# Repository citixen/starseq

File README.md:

# starseq — project overview

This project and all files in it represent the state of the project as it was during EMF Camp 2026, where it ran as an installation (in the baking sun) for 4 days. It largely worked without incident for that time and the concept and implementation are at least a bit proven. However, the project is offered as-is and without any ability to support it further if you decide to try building one for yourself. It all works in my build, but that doesn't mean it will for you. I may have forgotten critical setup components, and I may have done something weird and forgotten to document it. Sorry if I did. I've also not really documented any of the specifics of how I wired it together in my build. It was horrible spaghetti (see pics) and you can definitely do better just using the pin allocations in the code to guide you. Best of luck! Use this as a jumping off point to something bigger and better! I know I will!

---

## what starseq is

**starseq** is an 8-track MIDI step sequencer whose musical content is generated from the real-time positions of naked-eye-visible stars in the sky above the instrument's physical location. Each of the 8 tracks claims a wedge ("slice") of the compass — a band of azimuth and a brightness threshold — and turns whichever stars currently sit inside that wedge into a step sequence: azimuth decides *when* (which step) a note falls, altitude decides *what pitch*, and brightness/colour decide *how loud* and *how long*. Because the sky moves, the sequences drift and evolve on their own, in real astronomical time or sped up/slowed/reversed via a simulated clock. Planets and constellation lines are drawn for visual context only currently — but the data is there for future uses.

The instrument is physically and electronically a three-tier system:

```
┌──────────────────────┐      ┌──────────────────────┐     ┌─────────────────────┐
│ 8 × Instrument       │      │ Controller Interface │     │ Sequencer           │
│ Controllers          │────▶│  (aggregator)        │────▶│ (Raspberry Pi 5)    │
│ (one per track)      │ UART │ RP2040 Pico          │ UART│ Sky engine, MIDI,   │
│ 9 pots + 2 switches  │      │                      │     │ display, output     │
│ + button + OLED      │      │                      │     │                     │
└──────────────────────┘      └──────────────────────┘     └─────────────────────┘
     ESP32-S3 DevKit             8-port aggregator            pygame + skyfield
     per track                  → single uplink               + MIDI + GPIO
```

A performer turns physical pots on 8 identical hand controllers; those settings flow up through an aggregating interface board to a Raspberry Pi, which combines them with live sky data to produce and play an 8-track MIDI sequence, rendered simultaneously as a star-dome visualisation.

The instrument is housed in a standard cheap 104hp eurorack case, with some cheap bulkhead pass-thrus to get USB and HDMI from the Pi outside the case, and to get power in.

---

## tier 1 — instrument controller (one per track, ×8)

**Hardware:** ESP32-S3 DevKit C-1 (cheap - and has 2 x 12-bit SAR ADCs). Per unit: 9 potentiometers, 2 SPDT switches (Mute/Stop; Mono/Poly), 1 momentary push-button (play direction), a 128×64 SSD1306 2 colour (yellow/blue) OLED over I2C (mounted inverted, yellow  strip at the bottom), and a UART link out to the Controller Interface. The PCB files are included for the version used at EMF 26. These were made quickly and down to a price. Better board layouts and control configurations can be achieved!

**Role:** turn physical control positions into a per-track parameter packet and keep the OLED showing current state.

In the published firmware, all 9 pots are live simultaneously on a single page (an earlier multi-page design was collapsed to one page for simplicity). Each pot drives one parameter directly: length, base note, note range, slice centre, step divider, slice width, play mode, slice brightness, and duration max (which rescales live across `1…current length`). The two switches and the button cover mute/stop, mono/poly, and play-direction toggle. Parameters that are sent from the controller but which no longer have a dedicated pot in this  revision — velocity lo/hi, duration lo, parameter mode, MIDI channel — are  held at fixed firmware defaults but are still transmitted in full on every  packet, because **the wire format was deliberately left unchanged** from an  earlier, fuller-featured revision. This means the interface and sequencer  require no changes to accept this simplified controller, and a future firmware  revision could re-expose those parameters on interface pages without touching  downstream code.

The controller debounces inputs, applies deadbanding to pot readings to try  to avoid flooding the serial link with jitter, and transmits change-driven updates plus a periodic heartbeat. It persists its working state to the ESP32's flash-backed NVS (a packed, versioned, CRC-checked 22-byte struct), so a power cycle resumes the previous session instead of resetting to defaults — with **pick-up logic** at boot only: a restored pot value is shown with a directional arrow on the OLED until the performer physically turns that pot through the stored value, at which point it goes live.

---

## tier 2 — controller interface (aggregator)

**Hardware:** a single Raspberry Pi Pico (RP2040), with 8 independent PIO-UART port pairs (one RX/TX pair per controller) plus one hardware UART uplink to the Raspberry Pi. All built onto a small vero board, along with power distribution for the controllers. Takes in a single USB-C connection for 5V.

**Role:** a hardware-agnostic multiplexer. It runs 8 concurrent per-port receivers, validates and decodes each controller's packet (frame boundaries, protocol version, CRC, field ranges), maintains a live state table (one record per controller, with sequence number, last-RX timestamp, and a waiting/online/stale/offline status derived from timeout), and republishes that aggregated state upstream to the Pi as a single serial stream. A single-port fault never blocks the other 7 ports.

Two upstream message shapes exist: periodic **full snapshots** (all 8 controller records in one packet, sent roughly every 400 ms) and **delta packets** (a single controller's record, sent immediately whenever a field changes beyond a small deadband). This keeps the uplink responsive to live pot movement without needing to stream continuously.

---

## tier 3 — sequencer (Raspberry Pi 5)

**Hardware:** a Raspberry Pi 5, with a serial connection to the interface board, a 20 pulse rotary encoder and an SPDT connected to GPIO pins. Outputs HDMI, and has USB connections - all passed through the case.

**Role:** the brain of the instrument. Runs headlessly, receives the  aggregated controller state over serial, computes the live sky, turns  sky + per-track parameters into MIDI, and renders everything to an HDMI/DSI display via pygame.

### architecture

The application is a set of daemon background threads (Serial RX, Input Handler, Sky Engine, Sequence Builder, Sequencer Engine, MIDI Clock Input, GPS Receiver) plus one blocking main-thread loop for the pygame display — pygame's video backend must own the main thread on Linux/the Pi. Shared state moves through thread-safe primitives only: per-track locks, bounded queues, and a lock-free double-buffered (plus one "pending") sequence store per track. The sequencer engine requests real-time (`SCHED_FIFO`) scheduling and is never allowed to block on sky computation, serial I/O, GPS parsing, or rendering.

### midi generation

1. **Sky Engine** recomputes, on a fixed ~250 ms interval, the alt/az of    every star in the Yale Bright Star Catalogue (via Skyfield/DE421) and of     7 planets, using a **simulated clock** that can run at real speed, be     frozen, fast-forwarded, or reversed (a discrete multiplier ladder from     ‑64× to 64×), or jumped to an explicit date via a preset events picker     or manual date fields. Only stars above the horizon and brighter than     magnitude 6.5 (naked-eye) survive into the published snapshot; planets     are published on a separate, sequencing-blind channel.
2. **Sequence Builder** takes each track's slice (`slice_centre` ±    `slice_width/2`, wrap-around handled mod 360) and `slice_brightness`    (mapped to a magnitude cutoff), filters the star snapshot down to that    track's candidate stars, buckets them into steps by azimuth, assigns each    a MIDI note from altitude (mapped onto the valid in-scale notes within    `base_note … base_note + note_range`), and picks which candidate(s) in a    step actually sound according to the track's **play mode** (random,    highest, lowest, middle, first, last, brightest, dimmest) and mono/poly    mode. Velocity comes from magnitude and duration from B‑V colour index    (or from static/per-loop-randomised values, depending on `param_mode`).    Loop-randomised tracks stage their next sequence in a third "pending"    buffer so a re-roll never disturbs a note already playing mid-loop; the    swap happens only at that track's own loop boundary.
3. **Sequencer Engine** is the real-time clock: internal PPQN-24 tick    generation or external MIDI clock, per-track step/tick accumulators so    tracks can run at independent step-dividers while staying phase-locked,    forward/reverse play direction, note-on/note-off scheduling, and MIDI    output. It also drives the flash events consumed by the display so that    firing notes visibly pulse on the star dome and sequencer grid in the    same colour as the track that's playing them.
4. **MIDI channel routing** is decoupled from whatever channel a controller    itself reports: a transport-bar **CH MODE** setting chooses between the    controller-launch default, sequential per-track channels, all-tracks-on-    one-channel, or trusting the controller's own reported channel.

### display

A pygame UI running at 30 fps shows a polar-projected star dome (stars, planet hexagon markers, constellation lines), an 8-row sequencer grid, and an always-visible transport bar (no modal menu — a single focus pointer moves around a flat ring of stops for location, view/brightness toggles, tempo, clock source, key/scale, polyphony limit, MIDI device, channel mode, and simulated time). Layout adapts automatically to portrait, landscape, or extreme-aspect screens, and three independent brightness toggles plus a 10-mode **VIEW** setting control how much of the sky, wedges, and note flashes are visible without ever touching what's actually being sequenced.

### inputs

A rotary encoder + SPDT play/stop switch (GPIO on the Pi) provide local transport control, with a keyboard fallback for headless/dev use. Location can come from config defaults, manual entry, a USB NMEA GPS receiver, or a built-in list of preset cities — switchable live, without a restart.

---

## end-to-end data flow

```
Pot/switch/button position (Instrument Controller)
   → smoothed, deadbanded, mapped to parameter range
   → packed into a 21-byte controller record, COBS-framed, CRC-8
   → UART to Controller Interface

Controller Interface
   → validated per-port, staged into a per-controller state table
   → status (waiting/online/stale/offline) derived from packet recency
   → re-aggregated into full (8-record) or delta (1-record) packets
   → COBS-framed, CRC-8, UART uplink to Raspberry Pi

Raspberry Pi — Serial RX thread
   → CRC-checked, decoded, written directly into that track's TrackState
     under its lock; sequence_dirty = True

Sky Engine (independent of the above)
   → simulated time → star & planet alt/az → filtered snapshot published

Sequence Builder
   → combines the track's parameters with the star snapshot
   → produces a step sequence (notes, velocities, durations)

Sequencer Engine
   → ticks, advances steps, fires MIDI Note On/Off, schedules flash events

MIDI Output + Display
   → notes/clock out over MIDI; star dome & grid rendered in sync
```

A single 21-byte controller record schema is shared verbatim across all three tiers — the Instrument Controller populates it, the Controller Interface forwards it unmodified, and the Sequencer is the only tier that interprets it semantically (resolving the step-divider index to an actual ratio, applying channel-mode overrides, etc.).

---

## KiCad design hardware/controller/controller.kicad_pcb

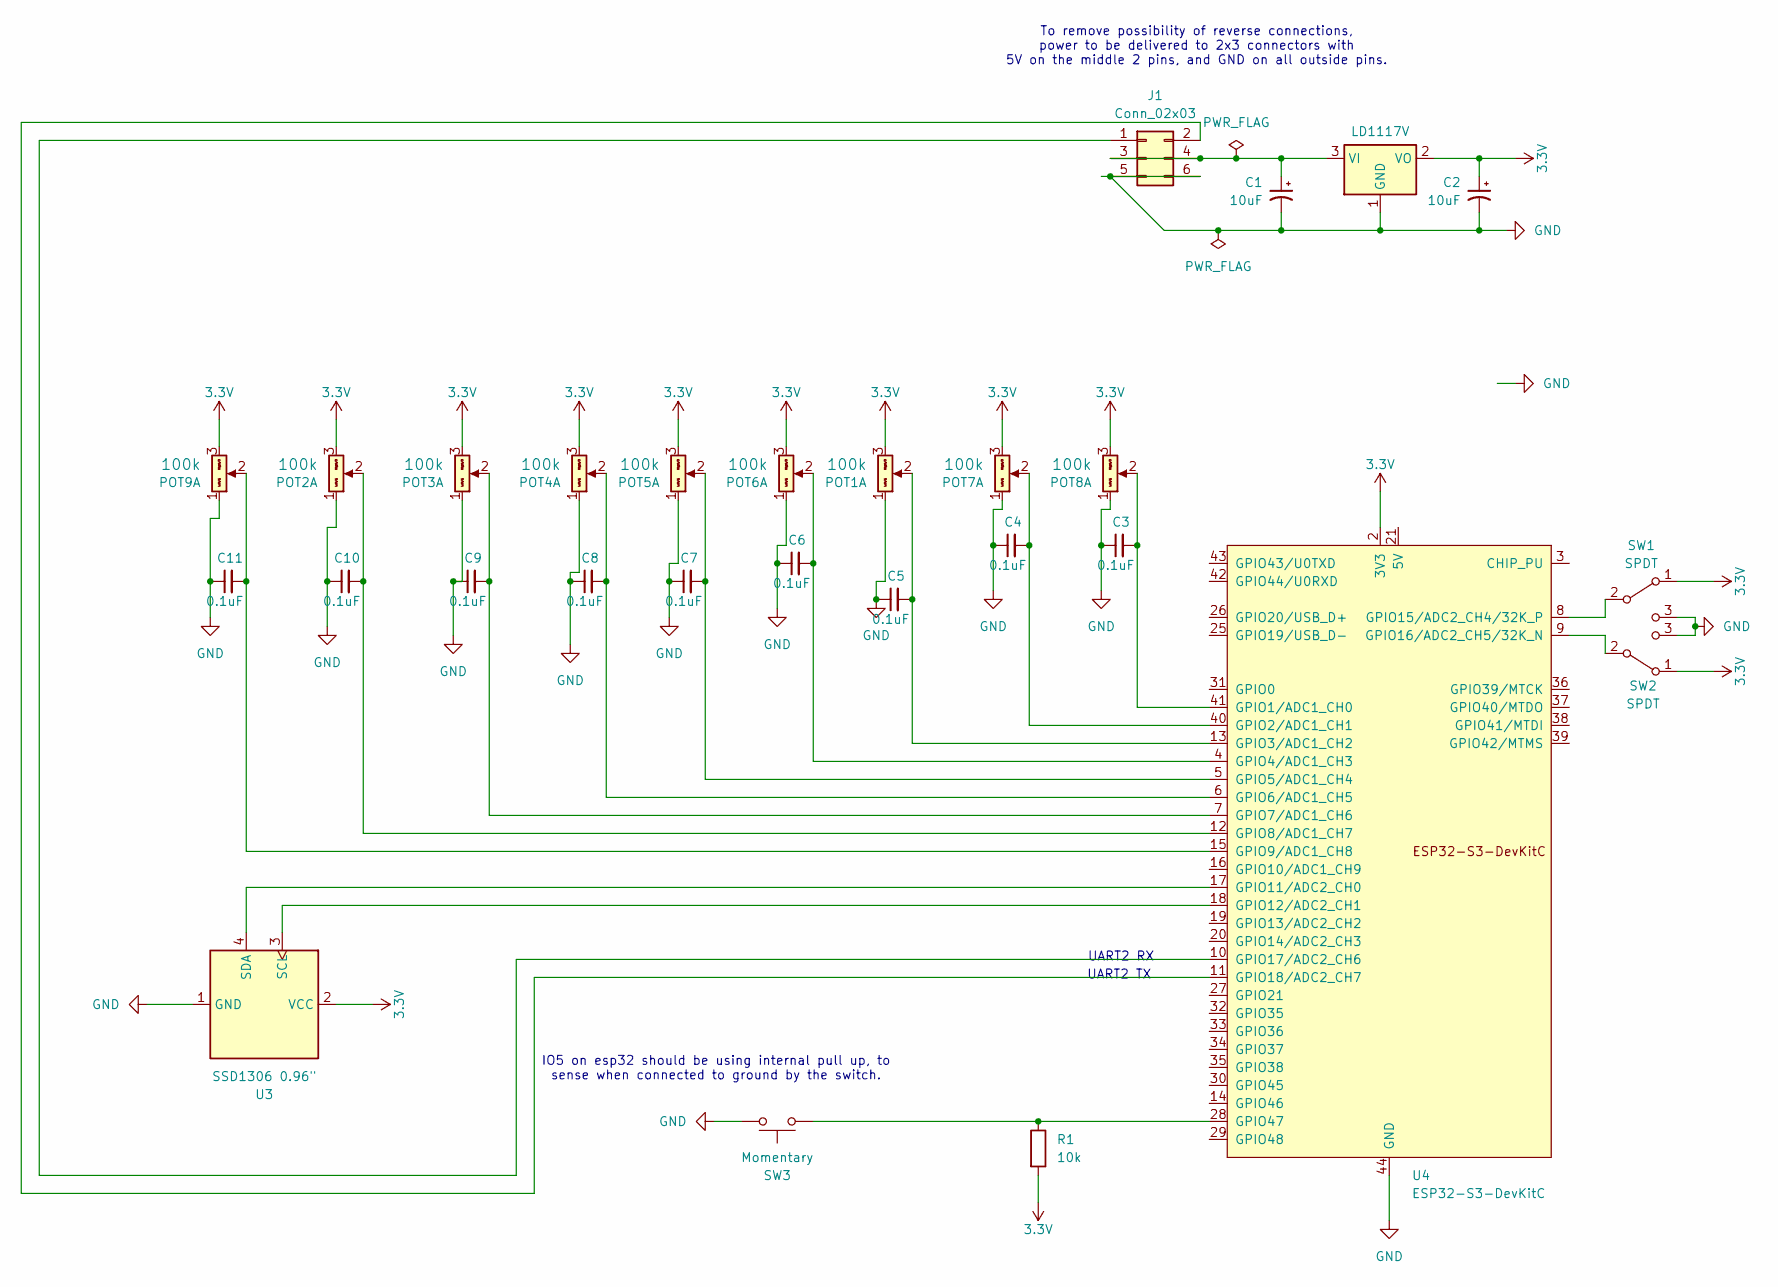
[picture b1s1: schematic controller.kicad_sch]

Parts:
C1, C2: 10uF; CP_Radial_D5.0mm_P2.50mm; Part Number EEE-FN1A100R; JLCPCB ID C176661
C3, C4, C5, C6, C7, C8, C9, C10, C11: 0.1uF; C_0805_2012Metric_Pad1.18x1.45mm_HandSolder; Voltage 25V; Tolerance 20%
J1: Conn_02x03; PinHeader_2x03_P2.54mm_Vertical
POT1, POT2, POT3, POT4, POT5, POT6, POT7, POT8, POT9: 9mm_NoDet_100k_Knurled_Lined; Pot_9mm_regularstylewiderleg; Part Number RV16AF-4A-15FW-B100K-3
R1: R_Generic; R_Axial_DIN0207_L6.3mm_D2.5mm_P10.16mm_Horizontal
SW1, SW2: SPDT; Switch_Toggle_SPDT_SubMini
SW3: Momentary; SW_PUSH_6mm
U2: LD1117V; TO-220-3_Horizontal_TabDown
U3: SSD1306 0.96"; 128x64OLED 0.96
U4: ESP32-S3-DevKitC; ESP32-S3-DevKitC-WIDER

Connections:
3.3V: C2.1, POT1.3 (Right), POT2.3 (Right), POT3.3 (Right), POT4.3 (Right), POT5.3 (Right), POT6.3 (Right), POT7.3 (Right), POT8.3 (Right), POT9.3 (Right), R1.2, SW1.1 (A), SW2.1 (A), U2.2 (VO), U3.2 (VCC), U4.1 (3V3), U4.2 (3V3)
GND: C1.2, C2.2, C3.1, C4.1, C5.1, C6.1, C7.1, C8.1, C9.1, C10.1, C11.1, J1.5, J1.6, POT1.1 (Left), POT2.1 (Left), POT3.1 (Left), POT4.1 (Left), POT5.1 (Left), POT6.1 (Left), POT7.1 (Left), POT8.1 (Left), POT9.1 (Left), SW1.3 (C), SW2.3 (C), SW3.2, U2.1 (GND), U3.1 (GND), U4.22 (GND), U4.23 (GND), U4.24 (GND), U4.44 (GND)
unnamed: C5.2, POT1.2 (Center), U4.13 (GPIO3/ADC1_CH2)
unnamed: C10.2, POT2.2 (Center), U4.12 (GPIO8/ADC1_CH7)
unnamed: C9.2, POT3.2 (Center), U4.7 (GPIO7/ADC1_CH6)
unnamed: C8.2, POT4.2 (Center), U4.6 (GPIO6/ADC1_CH5)
unnamed: C7.2, POT5.2 (Center), U4.5 (GPIO5/ADC1_CH4)
unnamed: C6.2, POT6.2 (Center), U4.4 (GPIO4/ADC1_CH3)
unnamed: C4.2, POT7.2 (Center), U4.40 (GPIO2/ADC1_CH1)
unnamed: C3.2, POT8.2 (Center), U4.41 (GPIO1/ADC1_CH0)
unnamed: C11.2, POT9.2 (Center), U4.15 (GPIO9/ADC1_CH8)
unnamed: SW1.2 (B), U4.8 (GPIO15/ADC2_CH4/32K_P)
unnamed: SW2.2 (B), U4.9 (GPIO16/ADC2_CH5/32K_N)
unnamed: C1.1, J1.3, J1.4, U2.3 (VI)
unnamed: U3.3 (SCL), U4.18 (GPIO12/ADC2_CH1)
unnamed: U3.4 (SDA), U4.17 (GPIO11/ADC2_CH0)
unnamed: J1.1, U4.10 (GPIO17/ADC2_CH6)
unnamed: J1.2, U4.11 (GPIO18/ADC2_CH7)
unnamed: R1.1, SW3.1, U4.28 (GPIO47)

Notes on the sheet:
UART2 RX
To remove possibility of reverse connections, power to be delivered to 2x3 connectors with 5V on the middle 2 pins, and GND on all outside pins.
UART2 TX
IO5 on esp32 should be using internal pull up, to sense when connected to ground by the switch.

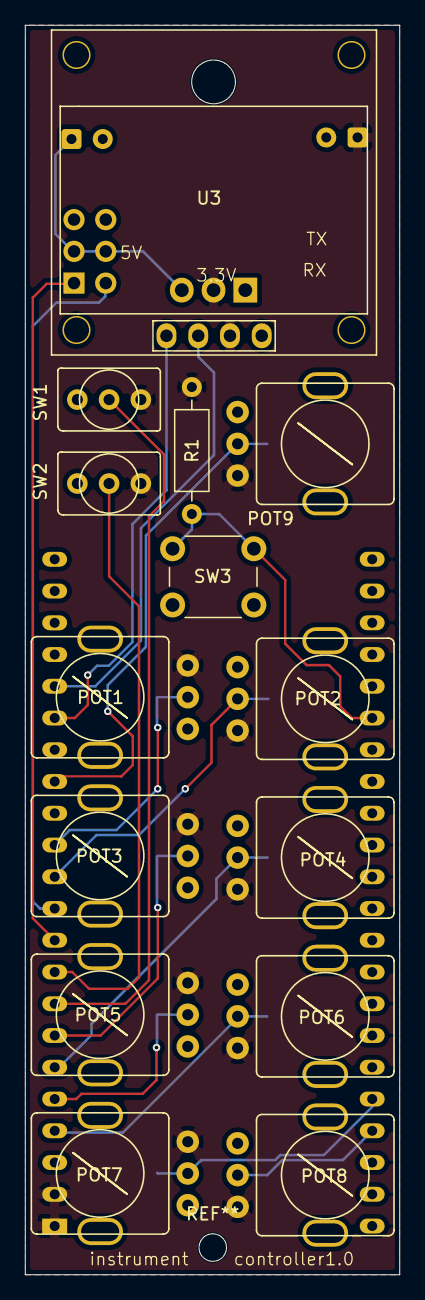
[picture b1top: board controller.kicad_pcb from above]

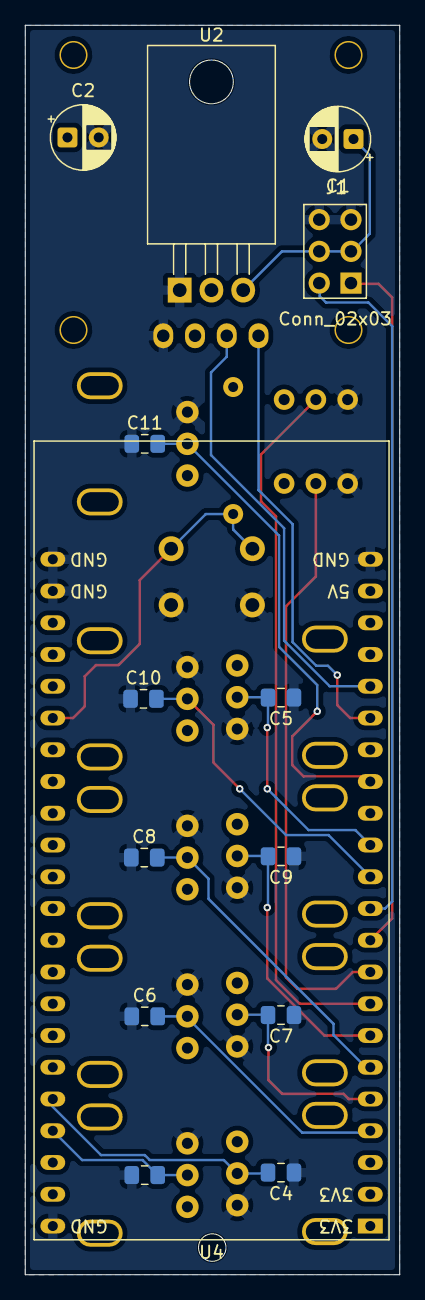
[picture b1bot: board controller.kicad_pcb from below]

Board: 2 copper layers, 30.0 x 99.9 mm, 28 parts (14 on the bottom side), 19 nets.

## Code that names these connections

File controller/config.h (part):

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//  persisted state.
//
// ---------------------------------------------------------------------------
#define PIN_POT1     9      // Length          — GPIO3  (also U0RXD; fine after boot)
#define PIN_POT2     3      // Base note        — GPIO8
#define PIN_POT3     8      // Note range       — GPIO7
#define PIN_POT4     7      // Slice centre     — GPIO6
#define PIN_POT5     6      // Step divider     — GPIO5
#define PIN_POT6     5      // Slice width      — GPIO4
#define PIN_POT7     4      // Play mode        — GPIO1
#define PIN_POT8     2      // Slice brightness — GPIO2
#define PIN_POT9     1      // Duration Hi      — GPIO9

// Digital inputs
#define PIN_SPDT1   15      // Mute/Stop switch     — GPIO15 (active HIGH)
#define PIN_SPDT2   16      // Mono/Poly switch     — GPIO16
#define PIN_BTN_DIR 47      // Direction toggle button — GPIO47

// ---------------------------------------------------------------------------
//  OLED I2C pin assignments  (from CONTROLLER_DESIGN.md)
//  Non-default I2C pins; Wire.begin() is called with these explicitly in
//  display_init()
// ---------------------------------------------------------------------------
#define PIN_I2C_SDA  11     // SDA — GPIO11
#define PIN_I2C_SCL  12     // SCL — GPIO12

// ---------------------------------------------------------------------------
//  OLED display parameters  (SSD1306 128×64, I2C)
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//  Serial uplink (Controller → Interface)
//  Uses UART1 (Serial1) with explicit pin assignment.
// ---------------------------------------------------------------------------
#define PIN_SERIAL_RX   17      // GPIO17 — RX from interface (future use)
#define PIN_SERIAL_TX   18      // GPIO18 — TX to interface
#define SERIAL_BAUD     57600

// Heartbeat interval — packet sent regardless of changes
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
